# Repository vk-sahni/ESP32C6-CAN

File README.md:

# ESP32-C6 CAN Telemetry Gateway

**A hardware design for an ESP32-C6 edge telemetry gateway for UAVs and robotics.** It is intended to sit alongside an ArduPilot flight controller and expose CAN / DroneCAN, Wi-Fi-capable MCU, USB-C, and MicroSD hardware interfaces. It is an auxiliary telemetry device, not a flight-controller replacement; gateway firmware and data services are not included.

> **Project status:** This repository contains KiCad hardware design files and derived documentation assets. It does not include gateway firmware, a telemetry decoder, a cloud service, or a dashboard. Network telemetry and local flight logging are planned system uses, not implemented or tested features.

## Key Features

- ESP32-C6FH4 MCU with integrated Wi-Fi radio and a U.FL RF connector path.
- TCAN332 3.3 V CAN transceiver with NUP2105L CAN-line protection.
- A fitted 120 ohm resistor across CANH and CANL.
- Four-position JST GH CAN connector with VBUS, CANH, CANL, and GND.
- MicroSD card socket and USB-C USB 2.0 interface.
- TC2014 3.3 V regulator, reset and boot switches, and auxiliary UART, I2C, and SPI headers.

These are hardware-design features only; no software operation is implied.

## Product Overview

The gateway is an edge device, not a flight controller replacement. The intended system puts the flight controller in charge of vehicle control and uses this board as a separate interface for telemetry experiments.

See [product.md](product.md) for a focused hardware description and [developement.md](developement.md) for the development workflow and validation record.

The architecture distinguishes **current hardware** from **planned software / cloud**. Internet access, backend ingestion, database storage, dashboard display, and MicroSD logging depend on firmware and services that are not present in this repository.

## PCB Design

The following views are rendered from the supplied KiCad PCB and its component models. The reverse-side view shows the actual board from below; it is intentionally not populated with imagined components.

The board outline dimensions shown in the PCB drawing are **40 x 25 mm**. This is a design dimension, not an enclosure or mechanical qualification. The KiCad stackup defines four copper layers.

## Hardware Architecture

Major circuit references:

| Function | Design reference | Schematic value / note |
|---|---|---|
| MCU | U1 | ESP32-C6FH4 |
| CAN transceiver | U3 | TCAN332, supplied from +3V3 |
| CAN protection | D3 | NUP2105L, connected to CANH, CANL, and GND |
| CAN shunt | R16 | 120 ohm across CANH and CANL |
| 3.3 V regulator | U2 | TC2014-3.3VxCTTR |
| MicroSD socket | J2 | DAT1 and DAT2 pins are marked no-connect |
| USB connector | J1 | USB 2.0 Type-C receptacle |
| RF connector | AE2 | KH5220-A36 U.FL footprint/model |
| USB VBUS protection | D2 | SZESD9B5.0ST5G |

The schematic also contains J4 UART telemetry, J5 I2C, and J6 External SPI connector blocks. Their presence does not indicate that any corresponding firmware interface is implemented.

## CAN Interface

J3 pinout from the schematic:

| J3 pin | Net / function |
|---:|---|
| 1 | VBUS |
| 2 | CANH |
| 3 | CANL |
| 4 | GND |

The schematic net names are `CANH` and `CANL`; the diagrams also use `CAN_H` and `CAN_L` for readability. R16 is drawn as a 120 ohm shunt across the pair. Check whether this fixed termination is appropriate for the board's position on the intended bus.

**Power caution:** J3 pin 1 is on the same VBUS net as the USB-C VBUS input and the input to U2. Review the complete system power arrangement before connecting independent supplies to USB-C and J3.

The TCAN332 symbol metadata describes a 1 Mbps-capable transceiver. The repository does not state or verify a project operating bit rate; no measured CAN performance is claimed.

## Wi-Fi and Internet Telemetry

The ESP32-C6FH4 includes a Wi-Fi radio, and the schematic routes its antenna connection through a matching network to AE2. This establishes the board-level RF path, not a validated antenna, range, regulatory result, or working network stack.

The intended uplink is:

```text
ArduPilot CAN / DroneCAN -> ESP32-C6 -> Wi-Fi -> Internet -> telemetry backend
```

Driver, DroneCAN parsing, data transport, cloud API, database, and dashboard software remain planned.

## MicroSD and Local Logging

J2 is a fitted MicroSD socket connected to SDIO-related MCU pins. DAT1 and DAT2 are explicitly marked no-connect in the schematic. The socket provides a hardware location for removable storage; card initialization, file format, flight logging, and recovery behavior are not implemented here.

## Telemetry Data Pipeline

The dashed blocks are planned firmware or cloud functions. No store-and-forward behavior is implemented or verified in this repository.

## ArduPilot / DroneCAN Integration

J3 is the board's CAN connector and is labeled `CAN` in the schematic. Before connecting it to a flight controller, verify connector wiring and polarity, bus termination, shared VBUS behavior, and the firmware's eventual protocol support. This repository does not include an ArduPilot integration guide, firmware, or a verified DroneCAN node implementation.

## Hardware Specifications

| Parameter | Design information |
|---|---|
| MCU | ESP32-C6FH4 |
| Wireless | ESP32-C6 integrated Wi-Fi radio; RF path to U.FL connector |
| CAN transceiver | TCAN332, 3.3 V supply in the schematic |
| CAN protection | NUP2105L |
| CAN shunt | 120 ohm, R16 across CANH / CANL |
| Local storage | MicroSD socket; DAT1 / DAT2 no-connect |
| USB | USB-C receptacle, USB 2.0 D+ / D- |
| Logic / peripheral rail | +3V3 net |
| Regulator | TC2014-3.3VxCTTR |
| CAN connector | 4-position JST GH footprint, J3 |
| PCB outline | 40 x 25 mm per board drawing |
| PCB stackup | Four copper layers per KiCad project |
| CAN rate | Not specified or tested by this project. The TCAN332 symbol metadata lists 1 Mbps capability only. |

Values above are taken from the schematic, PCB, and project stackup. They are not production tolerances, measured performance, environmental ratings, or system qualification results.

## Repository Structure

```text
.
|-- ESP32-C6FH4.kicad_pcb
|-- ESP32-C6FH4.kicad_pro
|-- ESP32-C6FH4.kicad_sch
|-- Connectors.kicad_sch
|-- lib/
|   |-- footprints.pretty/
|   |-- packages3d/
|   `-- symbol/
`-- docs/
  |-- 3d/
  |   |-- ESP32-C6-CAN.step
  |   |-- ESP32-C6-CAN-enclosure.step
  |   |-- ESP32-C6-CAN-enclosed-assembly.step
  |   `-- design_enclosure.py
    |-- diagrams/
    `-- images/
```

The KiCad project names are preserved. Custom ESP32-C6 footprint and symbol assets are under `lib/`.

## 3D CAD Model

[Download the board assembly STEP model](docs/3d/ESP32-C6-CAN.step). It was exported from the supplied KiCad PCB and available 3D models. Component coverage depends on the 3D models present in the design; the STEP file is a design visualization, not a mechanical tolerance model.

### Enclosure Prototype

The enclosure is a parametric, two-piece prototype sized around the supplied board STEP. The base has side openings for USB-C, the CAN and UART headers, I2C, and the combined MicroSD / external-SPI end. A top pass-through is aligned with the board's U.FL connector. The board rests on two modeled edge supports and its existing H1 hole; two lid keepers constrain the opposite board edge. No new PCB holes are assumed.

- [Enclosure-only STEP](docs/3d/ESP32-C6-CAN-enclosure.step)
- [Board-in-enclosure STEP assembly](docs/3d/ESP32-C6-CAN-enclosed-assembly.step)
- [Editable CadQuery generator](docs/3d/design_enclosure.py)

The current concept measures 48 x 33 x 13 mm overall. It is a geometry-checked prototype, not a manufacturing release: print tolerances, screw selection, heat dissipation, connector/cable access, RF performance, and fit under real components still need physical validation. The generator checks that the modeled base and lid do not intersect the supplied board STEP; that check is not a fit or reliability qualification.

Editable diagrams are in [`docs/diagrams/`](docs/diagrams/): [system architecture](docs/diagrams/system-architecture.svg), [CAN interface](docs/diagrams/can-interface.svg), [hardware block diagram](docs/diagrams/hardware-block-diagram.svg), and [telemetry data flow](docs/diagrams/telemetry-data-flow.svg).

## Releases and Packages

There are no published versioned releases or GitHub Packages for this project yet. Use the [GitHub Releases page](https://github.com/vish-official-2525/ESP32C6-CAN/releases) to check for future tagged hardware snapshots.

For this hardware project, a release archive is the appropriate distribution format for versioned KiCad sources and manufacturing exports such as Gerbers, drill files, BOM, and STEP. Those manufacturing bundles are not published yet. The current STEP model and KiCad sources remain available in this repository; there is no installable software package or firmware binary.

The current PCB DRC and schematic-parity findings are recorded below. A tagged fabrication release should wait until those findings are reviewed and the design has an explicit validation status.

## Schematic Overview

The schematic sheets are `ESP32-C6FH4.kicad_sch` and `Connectors.kicad_sch`.

## Project Status

| Area | Status |
|---|---|
| KiCad schematic and PCB | Present |
| Custom symbol, footprint, and 3D assets | Present |
| PCB render and STEP export | Present |
| ESP32-C6 gateway firmware | Not included |
| CAN / DroneCAN protocol processing | Not included |
| MicroSD flight logging | Not included |
| Wi-Fi telemetry transport | Not included |
| Cloud API, database, dashboard | Not included |
| Bench, RF, environmental, or flight validation | Not reported |

## Development Roadmap

- Implement and document the CAN driver and supported ArduPilot / DroneCAN messages.
- Define telemetry buffering and failure handling.
- Implement MicroSD initialization, logging format, and recovery behavior.
- Add Wi-Fi transport and document its security and reconnection behavior.
- Define a cloud protocol and backend only when an implementation exists.
- Resolve the recorded PCB DRC and schematic-parity findings, then document electrical and system validation.

## Reliability Considerations

A read-only KiCad PCB DRC run with schematic parity reported **154 violations**: 52 via-diameter, 52 annular-width, 38 copper-clearance, 4 hole-clearance, 3 hole-to-hole, 2 silkscreen-edge, 2 copper-edge-clearance, and 1 missing H2 footprint. Separately, the report lists local-override warnings for the J6 symbol/footprint value mismatch and J1 library-footprint mismatch. It also reported **2 schematic-parity issues** and **0 unconnected pads**. This is not a clean DRC result, and it should be reviewed before fabrication; no fixes were made as part of this documentation work.

No CAN bitrate, USB/SD behavior, Wi-Fi range, power/current rating, connector rating, operating temperature, EMI/ESD immunity, or flight safety claim has been validated by this repository. Perform design review and bench testing before connecting the board to flight-critical equipment.

## License

No `LICENSE` file is currently present. Until a license is added, reuse and redistribution permissions are not specified; do not assume the hardware files are licensed for a particular use.

## Author

Repository owner: [vish-official-2525](https://github.com/vish-official-2525).

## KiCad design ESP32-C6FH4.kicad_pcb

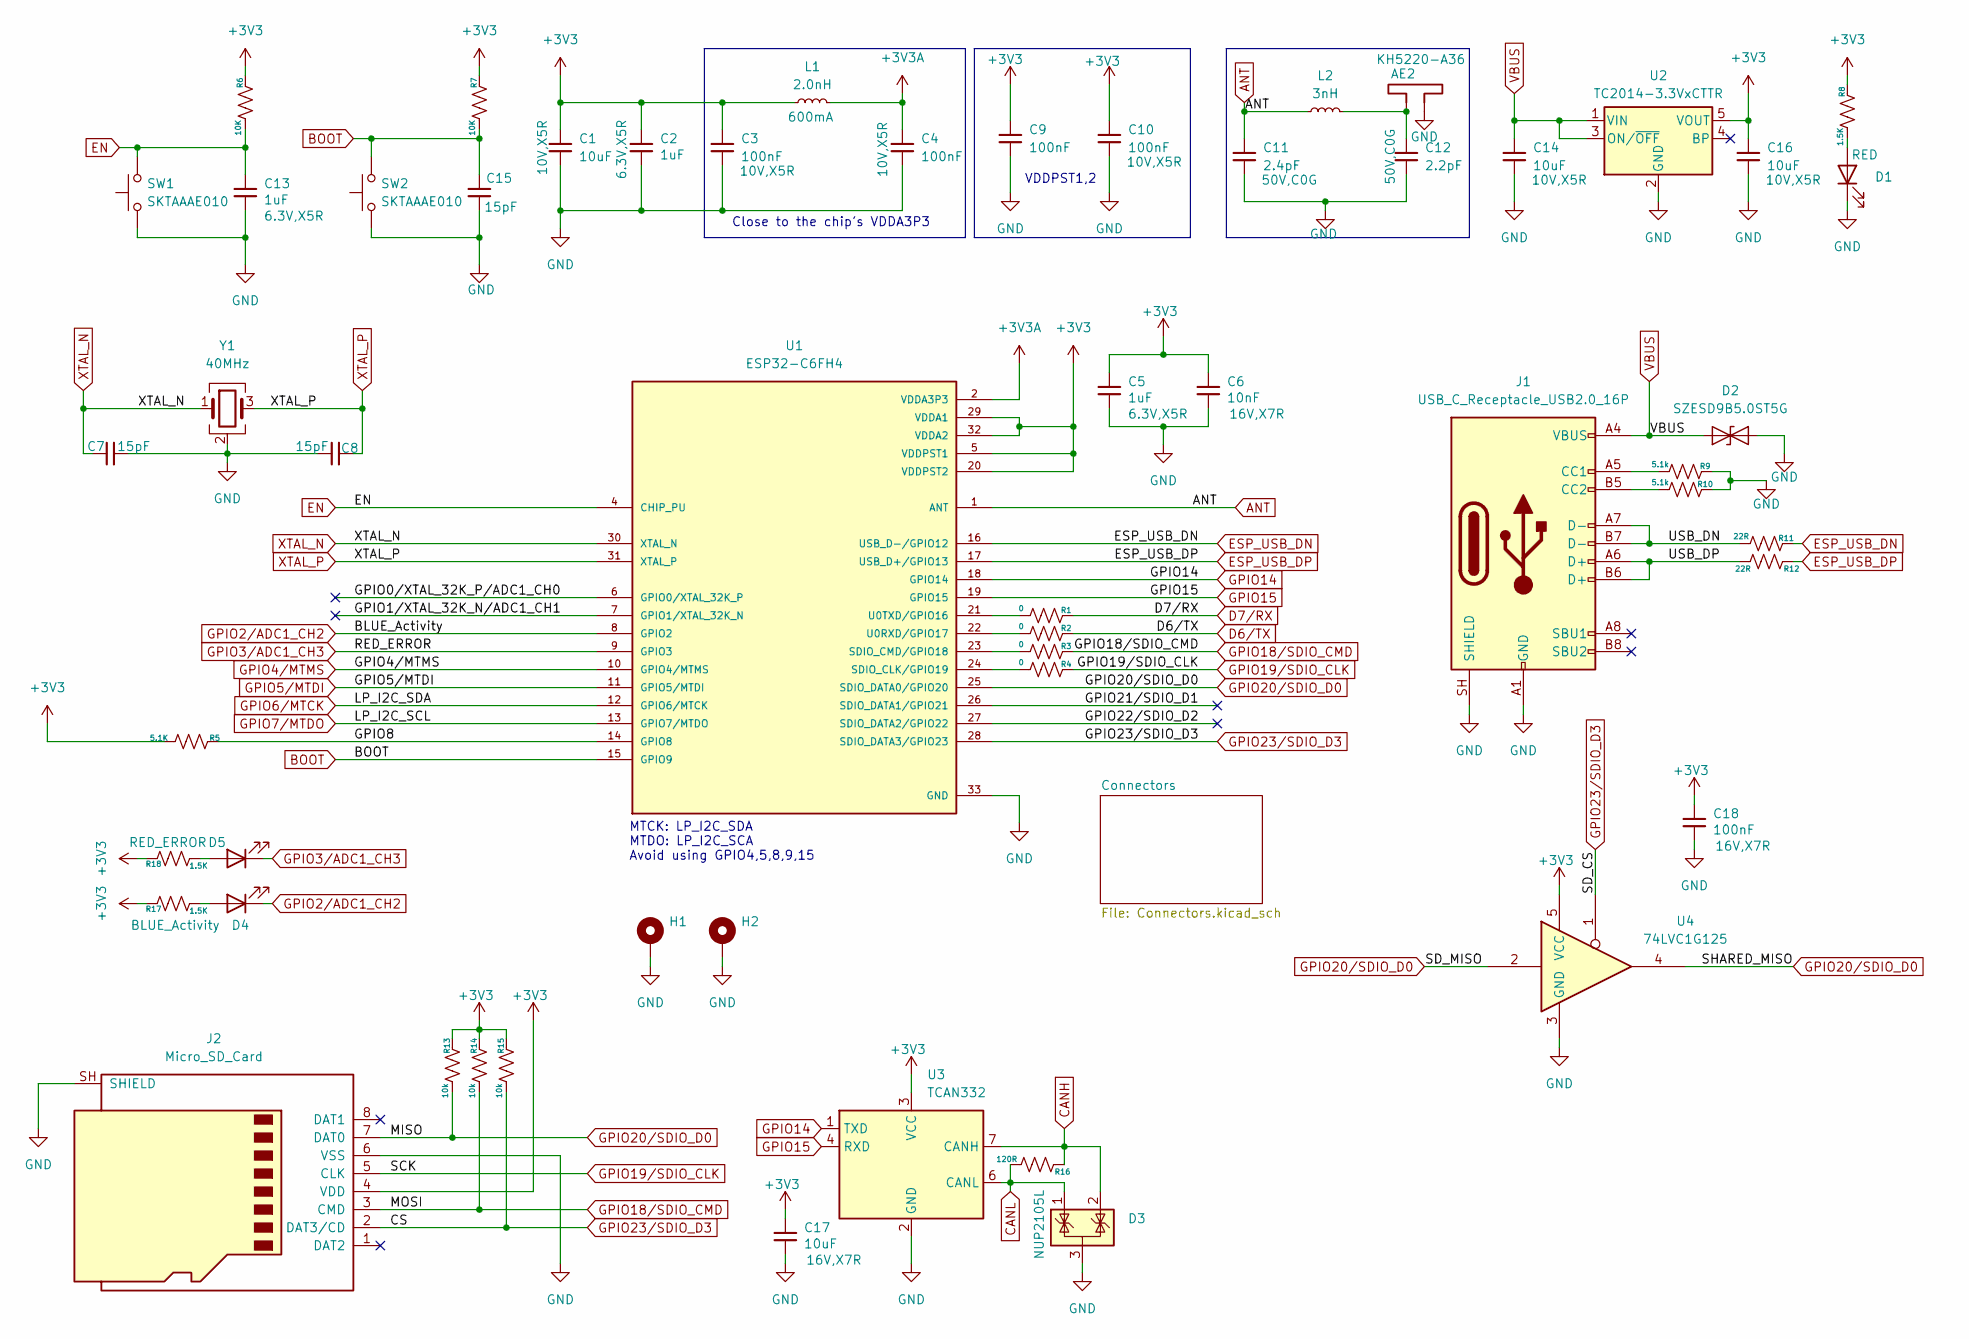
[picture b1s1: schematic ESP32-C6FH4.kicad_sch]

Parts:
AE2: KH5220-A36; U.FL_Molex_MCRF_73412-0110_Vertical
C1, C14, C16, C17: 10uF; C_0402_1005Metric
C2, C5, C13: 1uF; C_0402_1005Metric
C3, C4, C9, C10, C18: 100nF; C_0402_1005Metric
C6: 10nF; C_0402_1005Metric
C7, C8, C15: 15pF; C_0402_1005Metric
C11: 2.4pF; C_0402_1005Metric
C12: 2.2pF; C_0402_1005Metric
D1: RED; LED_0603_1608Metric
D2: SZESD9B5.0ST5G; D_SOD-923
D3: NUP2105L; SOT-23
D4: BLUE_Activity; LED_0603_1608Metric
D5: RED_ERROR; LED_0603_1608Metric
H1, H2: MountingHole_Pad; MountingHole_2.2mm_M2_Pad
J1: USB_C_Receptacle_USB2.0_16P; USB_C_Receptacle_GCT_USB4105-xx-A_16P_TopMnt_Horizontal
J2: Micro_SD_Card; microSD_HC_Wuerth_693072010801
L1: 2.0nH; L_0402_1005Metric
L2: 3nH; L_0402_1005Metric
R1, R2, R3, R4: 0; R_0402_1005Metric
R5: 5.1K; R_0402_1005Metric
R6, R7: 10K; R_0402_1005Metric
R8, R17, R18: 1.5K; R_0603_1608Metric
R9, R10: 5.1k; R_0402_1005Metric
R11, R12: 22R; R_0402_1005Metric
R13, R14, R15: 10k; R_0402_1005Metric
R16: 120R; R_0402_1005Metric
SW1, SW2: SKTAAAE010; SW_SPST_TS-1088-xR025
U1: ESP32-C6FH4; QFN50P500X500X90-33N; PARTREV v0.5
U2: TC2014-3.3VxCTTR; SOT-23-5
U3: TCAN332; TSOT-23-8
U4: 74LVC1G125; SOT-23-5
Y1: 40MHz; Crystal_SMD_0603-4Pin_6.0x3.5mm

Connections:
+3V3: C1.1, C2.1, C3.1, C5.1, C6.1, C9.1, C10.1, C16.1, C17.1, C18.1, J2.4 (VDD), L1.1, R5.1, R6.2, R7.2, R8.2, R13.2, R14.2, R15.2, R17.2, R18.2, U1.5 (VDDPST1), U1.20 (VDDPST2), U1.29 (VDDA1), U1.32 (VDDA2), U2.5 (VOUT), U3.3 (VCC), U4.5 (VCC); also elsewhere on the board
+3V3A: C4.1, L1.2, U1.2 (VDDA3P3), U1.3 (VDDA3P3)
/GPIO0/XTAL_32K_P/ADC1_CH0: U1.6 (GPIO0/XTAL_32K_P)
/GPIO1/XTAL_32K_N/ADC1_CH1: U1.7 (GPIO1/XTAL_32K_N)
/GPIO8: R5.2, U1.14 (GPIO8)
/GPIO21/SDIO_D1: U1.26 (SDIO_DATA1/GPIO21)
/GPIO22/SDIO_D2: U1.27 (SDIO_DATA2/GPIO22)
/USB_DN: J1.A7 (D-), J1.B7 (D-), R11.1
/USB_DP: J1.A6 (D+), J1.B6 (D+), R12.1
ANT: C11.1, L2.1, U1.1 (ANT)
BOOT: C15.2, R7.1, SW2.2, U1.15 (GPIO9)
CANH: D3.2 (K), R16.2, U3.7 (CANH); also elsewhere on the board
CANL: D3.1 (K), R16.1, U3.6 (CANL); also elsewhere on the board
D6/TX: R2.2; also elsewhere on the board
D7/RX: R1.2; also elsewhere on the board
EN: C13.1, R6.1, SW1.2, U1.4 (CHIP_PU)
ESP_USB_DN: R11.2, U1.16 (USB_D-/GPIO12)
ESP_USB_DP: R12.2, U1.17 (USB_D+/GPIO13)
GND: AE2.2, C1.2, C2.2, C3.2, C4.2, C5.2, C6.2, C7.2, C8.1, C9.2, C10.2, C11.2, C12.2, C13.2, C14.2, C15.1, C16.2, C17.2, C18.2, D1.1 (K), D2.1 (A1), D3.3 (A), H1.1 (1_1), H2.1, J1.A1 (GND), J1.A12 (GND), J1.B1 (GND), J1.B12 (GND), J1.SH (SHIELD), J2.6 (VSS), J2.SH (SHIELD), R9.2, R10.2, SW1.1, SW2.1, U1.33 (GND), U2.2 (GND), U3.2 (GND), U4.3 (GND), Y1.2 (G), Y1.4 (G); also elsewhere on the board
GPIO2/ADC1_CH2: D4.1 (K), U1.8 (GPIO2)
GPIO3/ADC1_CH3: D5.1 (K), U1.9 (GPIO3)
GPIO4/MTMS: U1.10 (GPIO4/MTMS)
GPIO5/MTDI: U1.11 (GPIO5/MTDI)
GPIO6/MTCK: U1.12 (GPIO6/MTCK); also elsewhere on the board
GPIO7/MTDO: U1.13 (GPIO7/MTDO); also elsewhere on the board
GPIO14: U1.18 (GPIO14), U3.1 (TXD)
GPIO15: U1.19 (GPIO15), U3.4 (RXD)
GPIO18/SDIO_CMD: J2.3 (CMD), R3.2, R14.1; also elsewhere on the board
GPIO19/SDIO_CLK: J2.5 (CLK), R4.2; also elsewhere on the board
GPIO20/SDIO_D0: J2.7 (DAT0), R13.1, U1.25 (SDIO_DATA0/GPIO20), U4.2, U4.4; also elsewhere on the board
GPIO23/SDIO_D3: J2.2 (DAT3/CD), R15.1, U1.28 (SDIO_DATA3/GPIO23), U4.1; also elsewhere on the board
unnamed: AE2.1, C12.1, L2.2
unnamed: D1.2 (A), R8.1
unnamed: D4.2 (A), R17.1
unnamed: D5.2 (A), R18.1
unnamed: J1.A5 (CC1), R9.1
unnamed: J1.B5 (CC2), R10.1
unnamed: R4.1, U1.24 (SDIO_CLK/GPIO19)
unnamed: R3.1, U1.23 (SDIO_CMD/GPIO18)
unnamed: R2.1, U1.22 (U0RXD/GPIO17)
unnamed: R1.1, U1.21 (U0TXD/GPIO16)
VBUS: C14.1, D2.2 (A2), J1.A4 (VBUS), J1.A9 (VBUS), J1.B4 (VBUS), J1.B9 (VBUS), U2.1 (VIN), U2.3 (ON/~OFF); also elsewhere on the board
XTAL_N: C7.1, U1.30 (XTAL_N), Y1.1
XTAL_P: C8.2, U1.31 (XTAL_P), Y1.3

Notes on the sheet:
VDDPST1,2
MTCK: LP_I2C_SDA MTDO: LP_I2C_SCA Avoid using GPIO4,5,8,9,15
Close to the chip's VDDA3P3

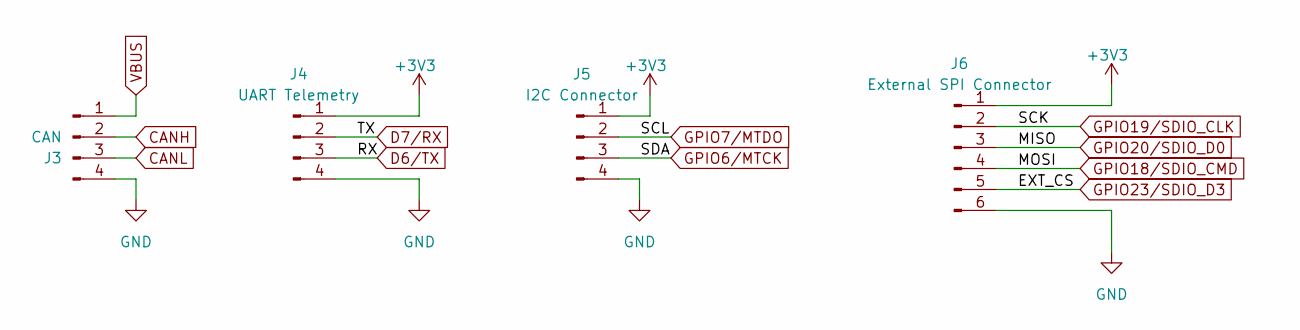
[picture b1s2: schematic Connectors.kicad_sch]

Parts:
J3: CAN; JST_GH_SM04B-GHS-TB_1x04-1MP_P1.25mm_Horizontal
J4: UART Telemetry; JST_GH_SM04B-GHS-TB_1x04-1MP_P1.25mm_Horizontal
J5: I2C Connector; JST_GH_SM04B-GHS-TB_1x04-1MP_P1.25mm_Horizontal
J6: External SPI Connector; JST_GH_SM06B-GHS-TB_1x06-1MP_P1.25mm_Horizontal

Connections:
+3V3: J4.1, J5.1, J6.1; also elsewhere on the board
CANH: J3.2; also elsewhere on the board
CANL: J3.3; also elsewhere on the board
D6/TX: J4.3; also elsewhere on the board
D7/RX: J4.2; also elsewhere on the board
GND: J3.4, J4.4, J5.4, J6.6; also elsewhere on the board
GPIO6/MTCK: J5.3; also elsewhere on the board
GPIO7/MTDO: J5.2; also elsewhere on the board
GPIO18/SDIO_CMD: J6.4; also elsewhere on the board
GPIO19/SDIO_CLK: J6.2; also elsewhere on the board
GPIO20/SDIO_D0: J6.3; also elsewhere on the board
GPIO23/SDIO_D3: J6.5; also elsewhere on the board
VBUS: J3.1; also elsewhere on the board

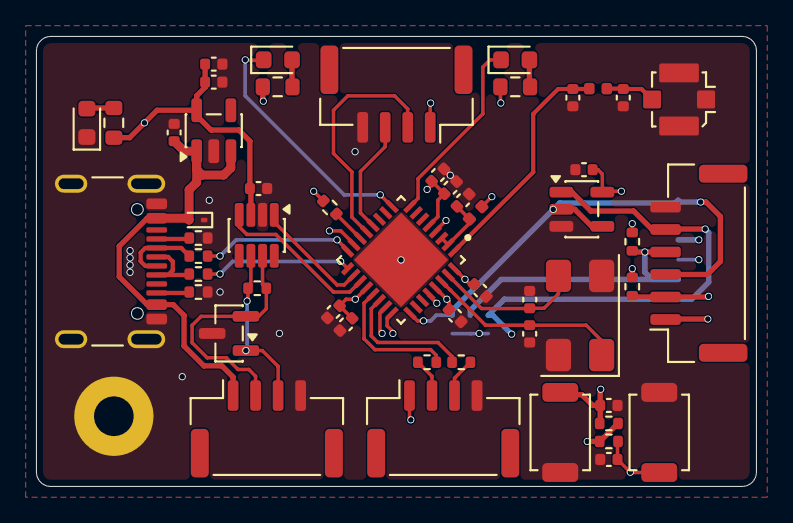
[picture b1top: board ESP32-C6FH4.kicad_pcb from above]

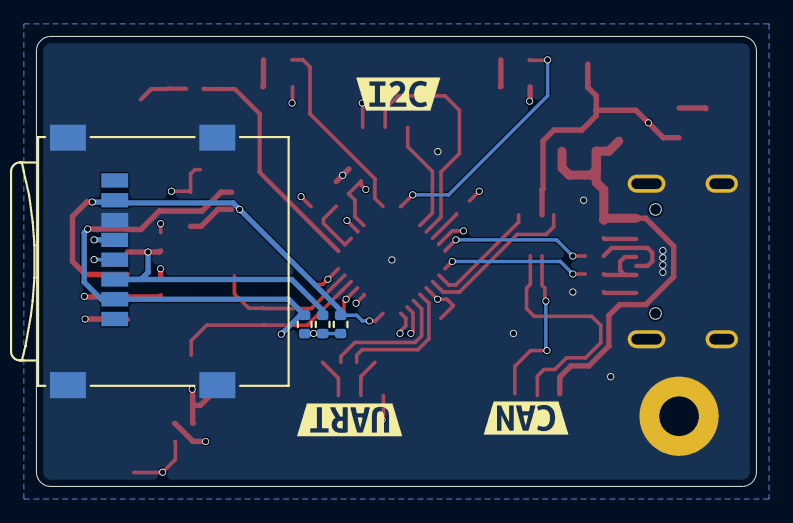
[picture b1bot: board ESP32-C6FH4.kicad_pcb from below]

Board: 4 copper layers, 40.0 x 25.0 mm, 61 parts (7 on the bottom side), 38 nets.

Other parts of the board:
kibuzzard-6AC1ACDB: G***; kibuzzard-6AC1ACDB
kibuzzard-6AC1ADD1: G***; kibuzzard-6AC1ADD1
kibuzzard-6AC1ADF5: G***; kibuzzard-6AC1ADF5
